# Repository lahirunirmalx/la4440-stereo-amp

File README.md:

# LA4440 stereo amplifier - volume header, toggle / GPIO mute, digital-pot ready

A 2 x 4 W stereo amplifier around the Sanyo LA4440, designed from parts in a hobby bin. Volume is a dual
100k linear pot on a 6-pin header that two X9C104 digital pots can replace later without touching the
board; mute works from a panel toggle now and from a microcontroller pin later, wired in parallel.
Every number below comes from ngspice. **No board has been built or measured yet.**

| Schematic | Board (both copper layers) | 3D top |
|---|---|---|
|  |  |  |

The full design notes, with the simulation tables, findings and an interactive CircuitJS model of one
channel, are in [docs/notes.html](docs/notes.html) (download and open it in a browser).

## What it does

| | |
|---|---|
| Output | 4.4 W per channel into 4 ohm at 13.2 V at the onset of clipping (3.7 W at 12 V); the datasheet's 6 W is at 10% THD |
| Gain | 30 dB (x33), set by 470 ohm in each feedback leg. The chip alone is 51.5 dB, which would reach full power at 18 mV in and leave the volume knob useless |
| Input for full power | 0.18 V peak with the volume at maximum |
| Bandwidth | 20 Hz (2200 uF into 4 ohm) to well above 20 kHz |
| Volume | dual B100K linear pot with 10k taper resistors: -18 dB at half travel, near-log. Drop-in: 2 x X9C104 on the same header |
| Mute | LA4440 pin 4, 6.9 mA from a toggle or from a 3.3 V GPIO (2N3904 + 2N5401 high-side switch); 40 dB per datasheet, 55 dB with the 5.6k input resistors |
| Supply | 12 to 15 V DC, 2 A (18 V absolute maximum) |
| Board | 90 x 70 mm, 2 layers, GND pour both sides, 4 x M2.5 corner holes; through-hole parts with SMD twins on the same pads, transistor pinout fields |

## Repository

| Path | What |
|---|---|
| `sim/` | ngspice decks behind every number, see [sim/README.md](sim/README.md) |
| `kicad/gen_sch.py` | writes the schematic `la4440.kicad_sch` (labels, custom LA4440 symbol in `la4440.kicad_sym`) |
| `kicad/run_checks.sh` | schematic -> netlist -> `netcheck.py` against `sim/amp_full.cir` -> ERC -> PDF / PNG |
| `kicad/gen_pcb.py`, `place.py` | places the board from the netlist (hybrid footprints are written to `Custom.pretty`) |
| `kicad/build_pcb.sh` | place -> freerouting -> GND pours -> DRC with schematic parity |
| `kicad/build_all.sh` | everything above plus 3D renders, Gerbers and the 2-up panel |
| `kicad/la4440-gerbers.zip`, `kicad/panel/` | fab files, see [ORDER_GUIDE.md](ORDER_GUIDE.md) |
| `bom.md` | parts, marked in hand / buy |
| `docs/notes.html` | design notes |

Status of the checks at the last build: netlist matches the simulation deck, ERC 0 errors, DRC 0 errors
with schematic parity (warnings left: silkscreen overlaps and the off-board parts RV1/RV2, SW1, LS1, LS2,
which have no footprint on purpose). Autorouting with freerouting is not deterministic: a rebuild can land
the tracks differently; DRC is the judge.

Tools: KiCad 9.0, ngspice 42, freerouting 1.9, KiKit 1.8. The generators need KiCad's `pcbnew` Python
module (`/usr/bin/python3` on Ubuntu).

## Building it

1. Read [bom.md](bom.md) and [ORDER_GUIDE.md](ORDER_GUIDE.md).
2. Fit everything except U1's heatsink screw. Bolt the heatsink to the LA4440 tab and wire it to J7 (GND).
3. **First power-up with the whole board populated** (the 0.1 uF + 5 ohm Zobels and the bootstrap caps are part
   of the chip's stability), no input, no speakers: bench supply at 13.2 V with a 300 mA current limit.
   Expect about 100 mA and both outputs (U1 pins 10 and 12) near 6.8 V - half the supply. Look at pins 10
   and 12 with a scope as well: a multimeter cannot see oscillation.
4. Then speakers, a quiet source, volume up slowly, and the mute toggle.

Datasheet: Sanyo LA4440 (ENN750F). Pinout used: 1 NF1, 2 IN1, 3 pre-GND, 4 mute, 5 ripple filter, 6 IN2,
7 NF2, 8 GND2, 9 BS2, 10 OUT2, 11 VCC, 12 OUT1, 13 BS1, 14 GND1 (pin 1 on the left with the marking toward
you, pins down).

## License

CC BY-NC-SA 4.0, see [LICENSE](LICENSE). Build it, change it, share it; do not sell it.

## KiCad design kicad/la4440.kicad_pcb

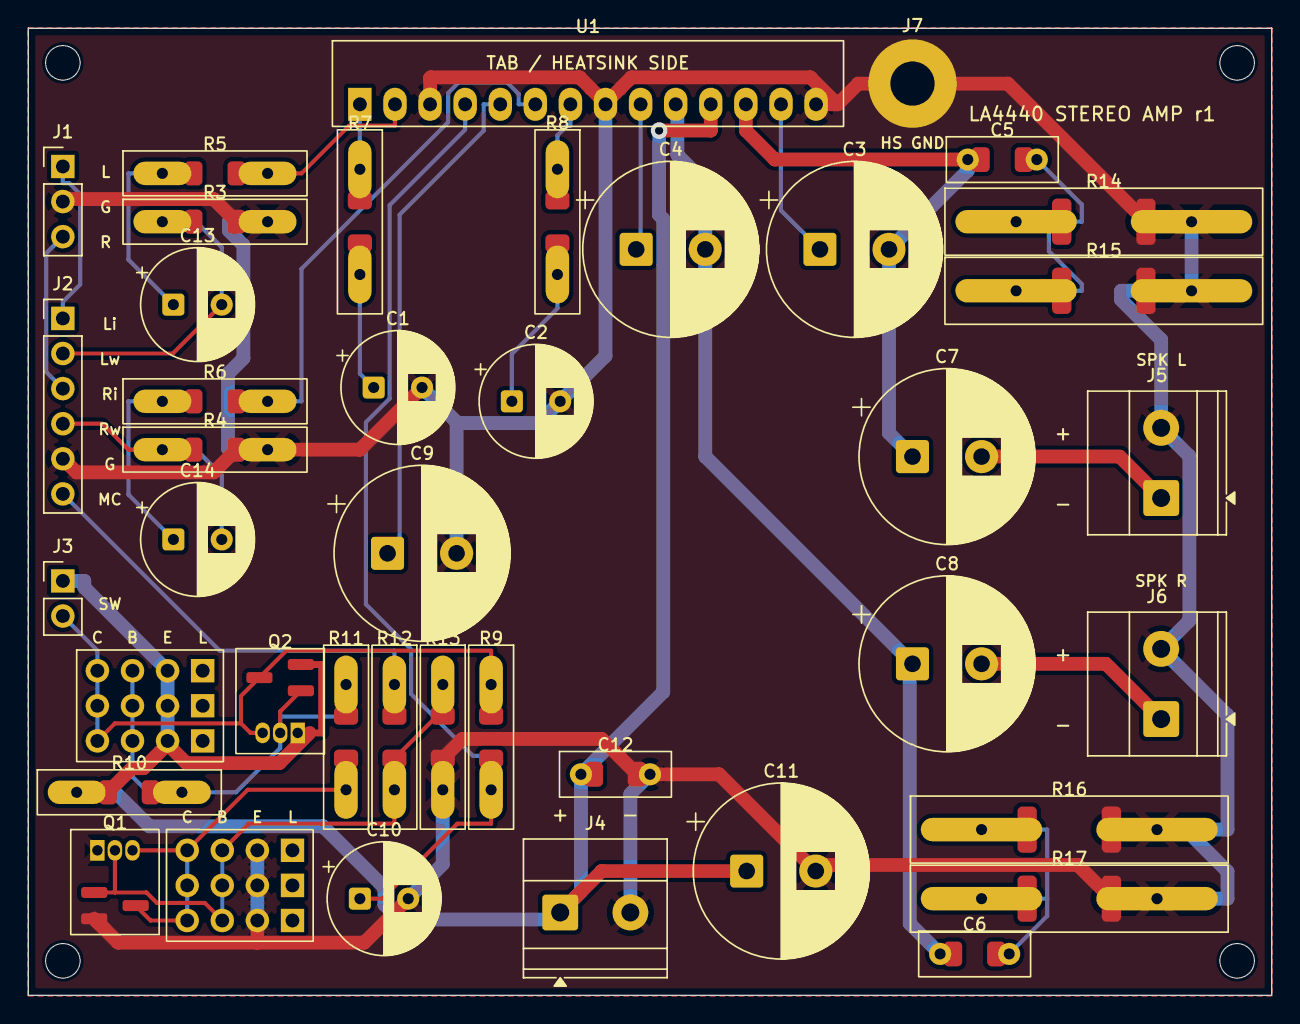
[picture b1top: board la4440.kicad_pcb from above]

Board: 2 copper layers, 90.0 x 70.0 mm, 45 parts (0 on the bottom side), 29 nets.

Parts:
C1, C2, C10, C13, C14: 47u 50V; CP_Radial_D8.0mm_P3.50mm
C3, C4, C9: 1000u 25V; CP_Radial_D12.5mm_P5.00mm
C5, C6: 0.1u film; C_Rect5_1206
C7, C8, C11: 2200u 25V; CP_Radial_D12.5mm_P5.00mm
C12: 0.1u; C_Rect5_1206
H1, H2, H3, H4: M2.5; Hole_2.5mm
J1: LINE IN L/GND/R; PinHeader_1x03_P2.54mm_Vertical
J2: VOLUME / CONTROL; PinHeader_1x06_P2.54mm_Vertical
J3: MUTE SWITCH; PinHeader_1x02_P2.54mm_Vertical
J4: DC IN +/-; TerminalBlock_Phoenix_MKDS-1,5-2-5.08_1x02_P5.08mm_Horizont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
J5: SPEAKER L; TerminalBlock_Phoenix_MKDS-1,5-2-5.08_1x02_P5.08mm_Horizont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
J6: SPEAKER R; TerminalBlock_Phoenix_MKDS-1,5-2-5.08_1x02_P5.08mm_Horizont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
J7: HEATSINK GND (M3 lug); MountingHole_3.2mm_M3_Pad
JQ1: Q1 2N3904 pinout field; JQ_3x4
JQ2: Q2 2N5401 pinout field; JQ_3x4
Q1: 2N3904; TO92_SOT23
Q2: 2N5401; TO92_SOT23
R3, R4, R11: 10k; R_Axial_1206
R5, R6: 5.6k; R_Axial_1206
R7, R8: 470; R_Axial_1206
R9: 1.8k; R_Axial_1206
R10: 47k; R_Axial_1206
R12: 4.7k; R_Axial_1206
R13: 100k; R_Axial_1206
R14, R15: 10R 1W (R1 pair); R_Axial10_2512
R16, R17: 10R 1W (R2 pair); R_Axial10_2512
U1: LA4440; SIP14H_LA4440

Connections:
/BS1: C3.1, U1.13
/BS2: C4.1, U1.9
/DC: C9.1, U1.5
/GND: C1.2, C2.2, C9.2, C10.2, C11.2, C12.2, C12.2S, J1.2, J2.5, J4.2, J5.2, J6.2, J7.1, JQ1.2, JQ1.6, JQ1.10, Q1.1, Q1.1S, R3.2, R3.2S, R4.2, R4.2S, R13.2, R13.2S, R14.2, R14.2S, R15.2, R15.2S, R16.2, R16.2S, R17.2, R17.2S, U1.3, U1.8, U1.14
/IN1: R5.2, R5.2S, U1.2
/IN2: R6.2, R6.2S, U1.6
/INL: J1.1, J2.1
/INR: J1.3, J2.3
/MUTE: C10.1, R9.2, R9.2S, U1.4
/MUTE_CTL: J2.6, R12.1, R12.1S
/MV: J3.2, JQ2.4, JQ2.8, JQ2.12, Q2.3, Q2.3S, R9.1, R9.1S
/NF1: R7.1, R7.1S, U1.1
/NF2: R8.1, R8.1S, U1.7
/NFC1: C1.1, R7.2, R7.2S
/NFC2: C2.1, R8.2, R8.2S
/OUT1: C3.2, C5.1, C5.1S, C7.1, U1.12
/OUT2: C4.2, C6.1, C6.1S, C8.1, U1.10
/PB: JQ2.3, JQ2.7, JQ2.11, Q2.2, Q2.2S, R10.2, R10.2S, R11.1, R11.1S
/Q1B: JQ1.3, JQ1.7, JQ1.11, Q1.2, Q1.2S, R12.2, R12.2S, R13.1, R13.1S
/Q1C: JQ1.4, JQ1.8, JQ1.12, Q1.3, Q1.3S, R11.2, R11.2S
/SPK1: C7.2, J5.1
/SPK2: C8.2, J6.1
/VCC: C11.1, C12.1, C12.1S, J3.1, J4.1, JQ2.2, JQ2.6, JQ2.10, Q2.1, Q2.1S, R10.1, R10.1S, U1.11
/W1: C13.1, R5.1, R5.1S
/W2: C14.1, R6.1, R6.1S
/WL: C13.2, J2.2, R3.1, R3.1S
/WR: C14.2, J2.4, R4.1, R4.1S
/ZB1: C5.2, C5.2S, R14.1, R14.1S, R15.1, R15.1S
/ZB2: C6.2, C6.2S, R16.1, R16.1S, R17.1, R17.1S

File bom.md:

# Bill of materials

Board: 90 x 70 mm, 2 layers. Every resistor, film cap and transistor position has through-hole holes
plus an SMD twin (1206 / 2512 / SOT-23) on the same net: fit either. Electrolytics are through-hole only.
"Stock" is the author's parts bin (`in hand`) versus what has to be ordered (`buy`).

Reference designators match the simulation deck `sim/amp_full.cir`, except: R14+R15 are the deck's R1
(two 10R in parallel), R16+R17 are R2, RV1/RV2 are the two gangs of the deck's RV1 (RV1AT/RV1AB, RV1BT/RV1BB).

## On the board

| Ref | Value | Footprint | Job | Stock |
|---|---|---|---|---|
| U1 | LA4440 (Sanyo) | SIP-14H, 2.54 mm | 2 x 6 W amplifier | in hand |
| R3, R4 | 10k 0.25 W 1% | axial 7.62 / 1206 | taper resistors (linear pot -> near-log law) | in hand |
| R5, R6 | 5.6k | axial 7.62 / 1206 | series input R, mute 40 -> 55 dB | in hand |
| R7, R8 | 470 | axial 7.62 / 1206 | RNF': gain 51.5 -> 30 dB. 1k for sources above 1 V (24.5 dB) | in hand |
| R9 | 1.8k | axial 7.62 / 1206 | mute pin current, 6.9 mA at 13.2 V | in hand |
| R10, R11, R12, R13 | 47k, 10k, 4.7k, 100k | axial 7.62 / 1206 | mute driver bias | in hand |
| R14, R15, R16, R17 | 10R 1 W | axial 12.7 / 2512 | Zobel resistors, two in parallel per channel (5 ohm) | in hand |
| C1, C2 | 47 uF 50 V | radial D8 P3.5 | feedback-leg caps (NF1, NF2) | in hand |
| C10 | 47 uF 50 V | radial D8 P3.5 | mute time constant (CO) | in hand |
| C13, C14 | 47 uF 50 V | radial D8 P3.5 | wiper coupling caps (pot scratch, X9C104 step clicks) | in hand |
| C3, C4 | 1000 uF 25 V | radial D12.5 P5 | bootstrap (datasheet 100 uF) | in hand |
| C9 | 1000 uF 25 V | radial D12.5 P5 | pin 5 ripple filter (datasheet 220 uF): slower, quieter start | in hand |
| C7, C8 | 2200 uF 25 V | radial D12.5 P5 | output caps, 18 Hz into 4 ohm | in hand |
| C11 | 2200 uF 25 V | radial D12.5 P5 | supply reservoir | in hand |
| Q1 | 2N3904 | TO-92 / SOT-23 + pinout field JQ1 | mute level shift | in hand |
| Q2 | 2N5401 | TO-92 / SOT-23 + pinout field JQ2 | mute high-side switch | in hand |
| J3 | 1x2 header | 2.54 mm | to the panel mute toggle SW1 | buy |
| C5, C6 | 0.1 uF polyester film, 50 V+ | 5 mm / 1206 | Zobel caps (datasheet requires film) | buy |
| C12 | 0.1 uF film or X7R | 5 mm / 1206 | supply decoupling at pin 11 | buy |
| J1 | 1x3 header | 2.54 mm | line in: L, GND, R | buy |
| J2 | 1x6 header | 2.54 mm | volume / control: 1 L in, 2 L wiper, 3 R in, 4 R wiper, 5 GND, 6 MUTE_CTL | buy |
| J4 | 2-pin screw terminal 5.08 mm | Phoenix MKDS-1,5 | DC in, 12 to 15 V (18 V max) | buy |
| J5, J6 | 2-pin screw terminal 5.08 mm | Phoenix MKDS-1,5 | speakers L, R | buy |
| J7 | M3 plated hole | 3.2 mm pad | heatsink to GND (datasheet: fin to GND) | (board) |

## Off the board

| Ref | Value | Job | Stock |
|---|---|---|---|
| SW1 | MTS-112 toggle (check it has the pins you need: SPST is enough) | manual mute, wired to J3 | in hand |
| RV1/RV2 | dual 100k LINEAR pot (B100K), on the panel, wired to J2 pins 1-5 | volume. Linear, not log, so two X9C104 can replace it with the same curve | buy |
| - | 2 x X9C104 (later) | digital volume on J2. Need 5 V and CS / INC / U-D from a microcontroller | in hand |
| LS1, LS2 | 4 to 8 ohm speakers | | buy |
| - | heatsink, about 5 C/W, two 3.4 mm holes 30 mm apart (the LA4440 tab), ground it with a wire to J7 | required | buy |
| - | 3.5 mm stereo jack, wired to J1 | | buy |
| - | 12 to 15 V DC 2 A adapter (or a bench supply) | | buy |

## Buy list

- 1 x dual 100k linear pot (B100K)
- 3 x 0.1 uF polyester film capacitor (C5, C6, C12)
- 1 x 1x3, 1 x 1x6, 1 x 1x2 pin header + mating plugs
- 3 x 2-pin 5.08 mm screw terminal
- 1 x heatsink for the LA4440, 3 x M3 screw + nut
- 1 x 3.5 mm stereo jack, 2 x speakers
- 1 x 12 to 15 V 2 A DC adapter
- 3 x 47 uF 50 V: only if the VLF receiver (another project on the same bench) is also built - this board uses all 5 in stock

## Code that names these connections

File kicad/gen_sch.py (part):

"""Generate la4440.kicad_sch + la4440.kicad_pro: LA4440 stereo amplifier with a
volume header (B100K now, 2 x X9C104 later) and toggle / GPIO mute.
Reference designators match ../sim/amp_full.cir and docs/notes.html.
Every pin gets a short stub and a net label; blocks are grouped on the sheet.
Run with /usr/bin/python3 (or any python3).
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    return round(n * 2.54, 2)


s = Sch("LA4440 stereo amplifier - volume header, toggle / GPIO mute")
U = s.lib("la4440", "LA4440", libfile=str(HERE / "la4440.kicad_sym"))
R = s.lib("Device", "R")
C = s.lib("Device", "C")
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part(R, "R6", "5.6k", 52, 34, {"1": "W2", "2": "IN2"}, fp=FP_R)

# ------------------------------------------------------------------ mute
block(4, 48, "MUTE: SW1 (off-board, J3) or MUTE_CTL high (GPIO) - wire-OR")
part(H2, "J3", "MUTE SWITCH", 8, 58, {"1": "VCC", "2": "MV"}, fp=FP_H2)
part(SPST, "SW1", "MTS-112 MUTE", 18, 58, {"1": "VCC", "2": "MV"}, on_board=False, lbl=(-4.0, -5.0))
part(R, "R10", "47k", 28, 58, {"1": "VCC", "2": "PB"}, fp=FP_R)
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# ------------------------------------------------------------------ pinout fields
block(4, 88, "TRANSISTOR PINOUT FIELDS: columns L E B C, rows = legs 1..3")
P = s.pin
for ref, val, gx, nets in (("JQ1", "Q1 2N3904 pinout field", 14, ("GND", "Q1B", "Q1C")),
                           ("JQ2", "Q2 2N5401 pinout field", 40, ("VCC", "PB", "MV"))):
    s.place(H12, ref, val, u(gx), u(100), 0, footprint=FP_JQ, ref_at=(u(gx) - 9.0, u(100) - 17.0),
            val_at=(u(gx) - 9.0, u(100) - 15.0))
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        s.label((px - 5.08, py), nets[col - 1], 180)

notes = [
    "Verified in ngspice (../sim/amp_full.cir): 30.3 dB, 20 Hz - 190 kHz, 4.4 W into 4R at 13.2 V before clipping, mute pin 6.9 mA.",
    "RV1 is a dual B100K LINEAR pot (or 2 x X9C104 on J2 later: they need 5 V and CS/INC/U-D from the ESP32). R3/R4 give it a near-log law.",
    "U1 heatsink tab to GND. Off-board: RV1/RV2 (dual pot), SW1, LS1, LS2. Not built yet - see docs/notes.html for the simulation and the unverified items.",
]
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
